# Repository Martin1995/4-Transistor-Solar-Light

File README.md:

# 4-Transistor-Solar-Light
KiCad Repo with Open Hardware Schematics and Board Files for building of small garden solar lights

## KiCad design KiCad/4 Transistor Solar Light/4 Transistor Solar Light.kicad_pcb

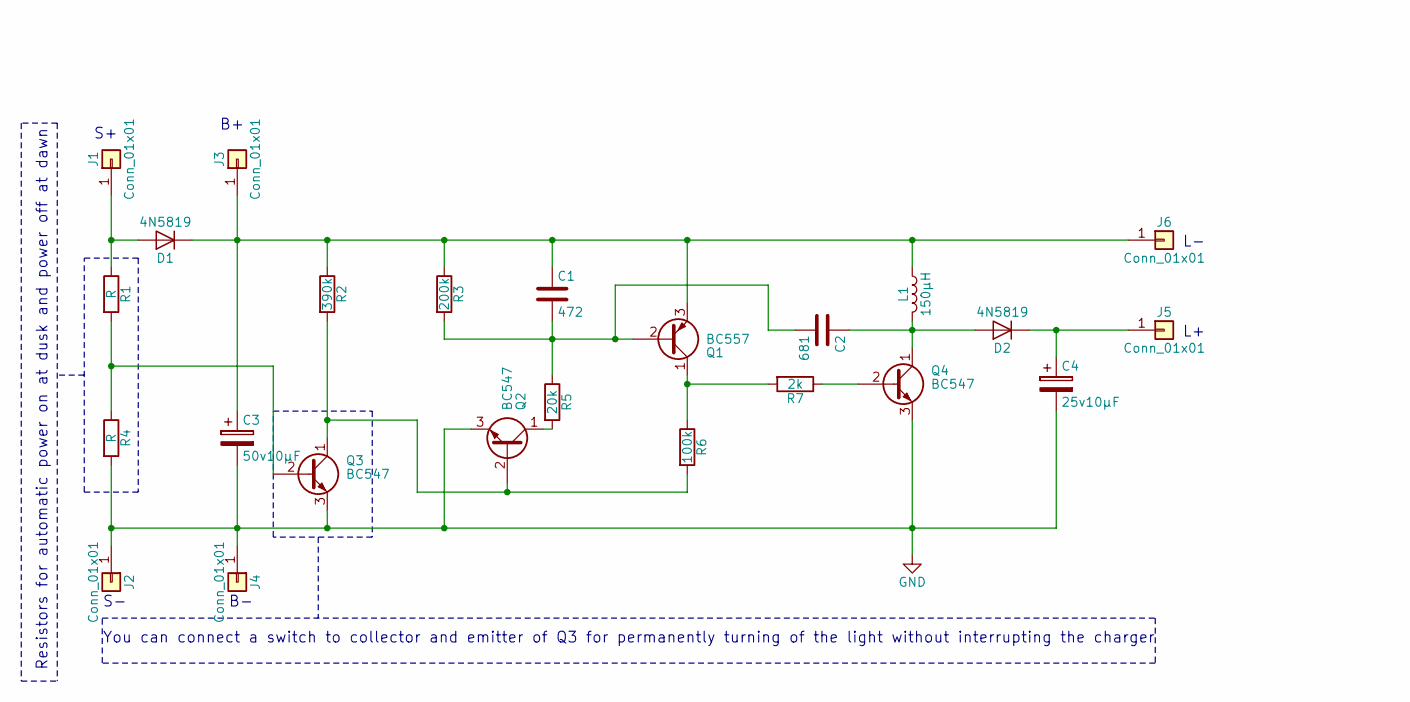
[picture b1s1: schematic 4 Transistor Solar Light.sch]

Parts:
C1: 472; C_Disc_D3.0mm_W1.6mm_P2.50mm
C2: 681; C_Disc_D3.0mm_W1.6mm_P2.50mm
C3: 50v10µF; CP_Radial_D5.0mm_P2.50mm
C4: 25v10µF; CP_Radial_D5.0mm_P2.50mm
D1, D2: 4N5819; D_A-405_P7.62mm_Horizontal
J1, J2, J3, J4, J5, J6: Conn_01x01; Pin_Header_Straight_1x01_Pitch2.00mm
L1: 150µH; L_Axial_L5.3mm_D2.2mm_P7.62mm_Horizontal_Vishay_IM-1
Q1: BC557; TO-92_Molded_Narrow
Q2, Q3, Q4: BC547; TO-92_Molded_Narrow
R1, R4: R; R_Axial_DIN0204_L3.6mm_D1.6mm_P5.08mm_Horizontal
R2: 390k; R_Axial_DIN0204_L3.6mm_D1.6mm_P5.08mm_Horizontal
R3: 200k; R_Axial_DIN0204_L3.6mm_D1.6mm_P5.08mm_Horizontal
R5: 20k; R_Axial_DIN0204_L3.6mm_D1.6mm_P5.08mm_Horizontal
R6: 100k; R_Axial_DIN0204_L3.6mm_D1.6mm_P5.08mm_Horizontal
R7: 2k; R_Axial_DIN0204_L3.6mm_D1.6mm_P5.08mm_Horizontal

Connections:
GND: C3.2, C4.2, J2.1, J4.1, Q2.3 (E), Q3.3 (E), Q4.3 (E), R4.2
unnamed: C1.1, C3.1, D1.1 (K), J3.1, J6.1, L1.1, Q1.3 (E), R2.1, R3.1
unnamed: C1.2, C2.2, Q1.2 (B), R3.2, R5.1
unnamed: C2.1, D2.2 (A), L1.2, Q4.1 (C)
unnamed: C4.1, D2.1 (K), J5.1
unnamed: D1.2 (A), J1.1, R1.1
unnamed: Q1.1 (C), R6.1, R7.2
unnamed: Q2.1 (C), R5.2
unnamed: Q2.2 (B), Q3.1 (C), R2.2, R6.2
unnamed: Q3.2 (B), R1.2, R4.1
unnamed: Q4.2 (B), R7.1

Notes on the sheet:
Resistors for automatic power on at dusk and power off at dawn
You can connect a switch to collector and emitter of Q3 for permanently turning of the light without interrupting the charger

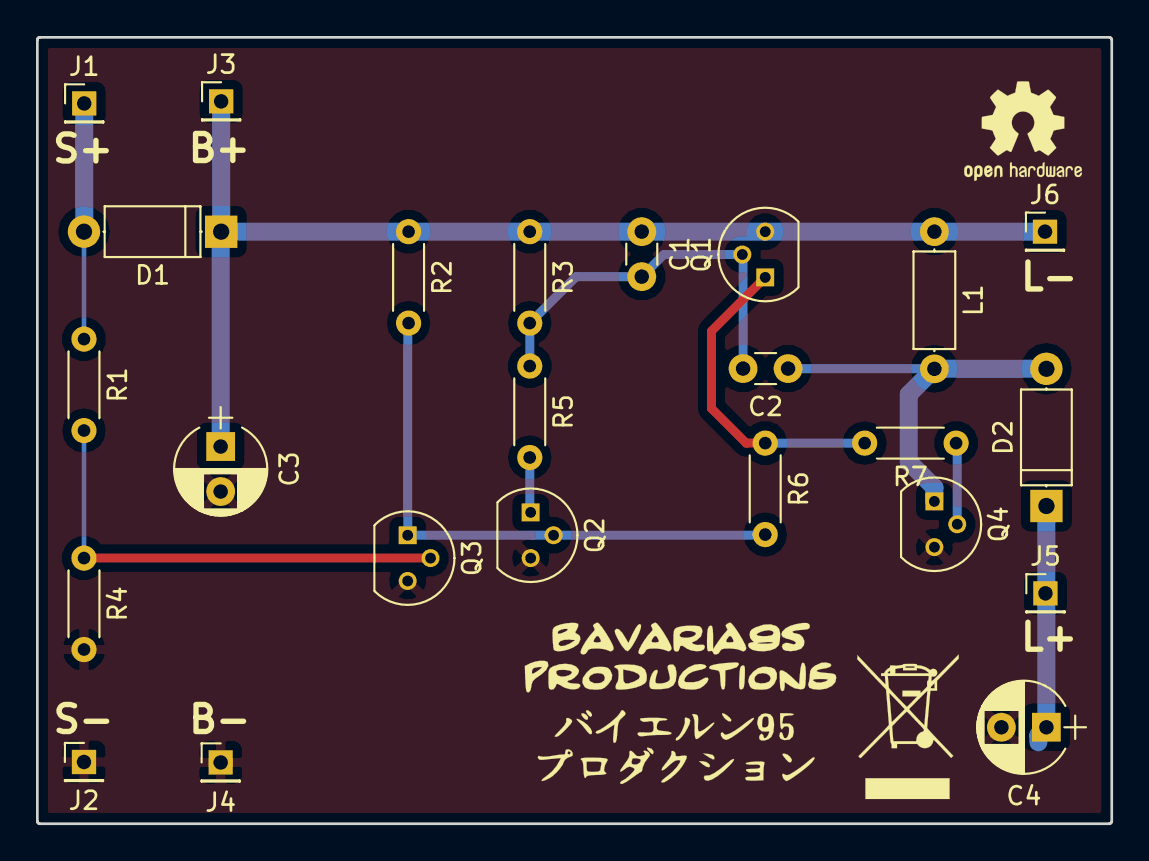
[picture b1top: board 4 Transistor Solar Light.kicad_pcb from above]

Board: 2 copper layers, 59.7 x 43.7 mm, 24 parts (0 on the bottom side), 11 nets.

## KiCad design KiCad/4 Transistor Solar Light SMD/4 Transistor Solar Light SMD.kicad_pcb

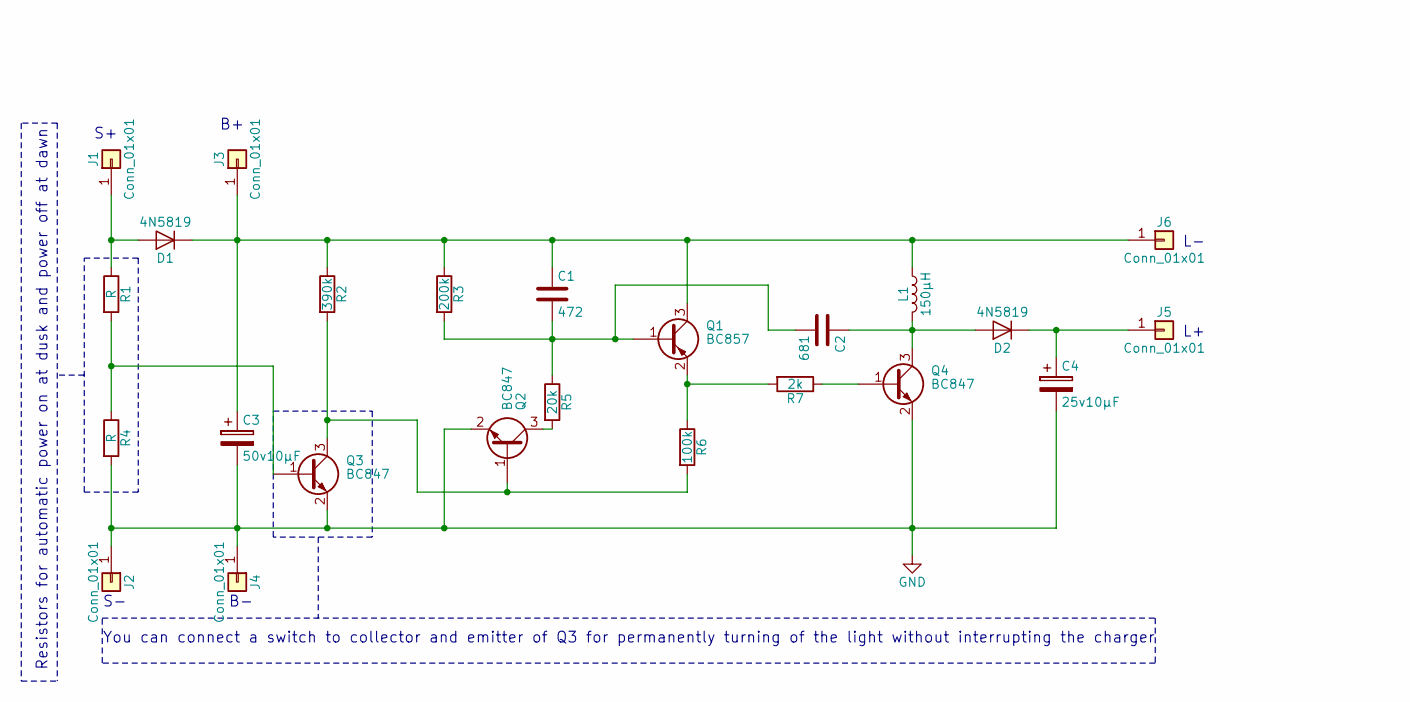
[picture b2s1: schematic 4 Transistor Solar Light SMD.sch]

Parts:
C1: 472; C_0805_HandSoldering
C2: 681; C_0805_HandSoldering
C3: 50v10µF; CP_Elec_4x5.8
C4: 25v10µF; CP_Elec_4x5.8
D1, D2: 4N5819; D_0805
J1, J2, J3, J4, J5, J6: Conn_01x01; Pin_Header_Straight_1x01_Pitch2.00mm
L1: 150µH; L_Axial_L5.3mm_D2.2mm_P7.62mm_Horizontal_Vishay_IM-1
Q1: BC857; SOT-23
Q2, Q3, Q4: BC847; SOT-23
R1, R4: R; R_0805_HandSoldering
R2: 390k; R_0805_HandSoldering
R3: 200k; R_0805_HandSoldering
R5: 20k; R_0805_HandSoldering
R6: 100k; R_0805_HandSoldering
R7: 2k; R_0805_HandSoldering

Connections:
GND: C3.2, C4.2, J2.1, J4.1, Q2.2 (E), Q3.2 (E), Q4.2 (E), R4.2
unnamed: C1.1, C3.1, D1.1 (K), J3.1, J6.1, L1.1, Q1.3 (C), R2.1, R3.1
unnamed: C1.2, C2.2, Q1.1 (B), R3.2, R5.1
unnamed: C2.1, D2.2 (A), L1.2, Q4.3 (C)
unnamed: C4.1, D2.1 (K), J5.1
unnamed: D1.2 (A), J1.1, R1.1
unnamed: Q1.2 (E), R6.1, R7.2
unnamed: Q2.1 (B), Q3.3 (C), R2.2, R6.2
unnamed: Q2.3 (C), R5.2
unnamed: Q3.1 (B), R1.2, R4.1
unnamed: Q4.1 (B), R7.1

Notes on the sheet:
Resistors for automatic power on at dusk and power off at dawn
You can connect a switch to collector and emitter of Q3 for permanently turning of the light without interrupting the charger

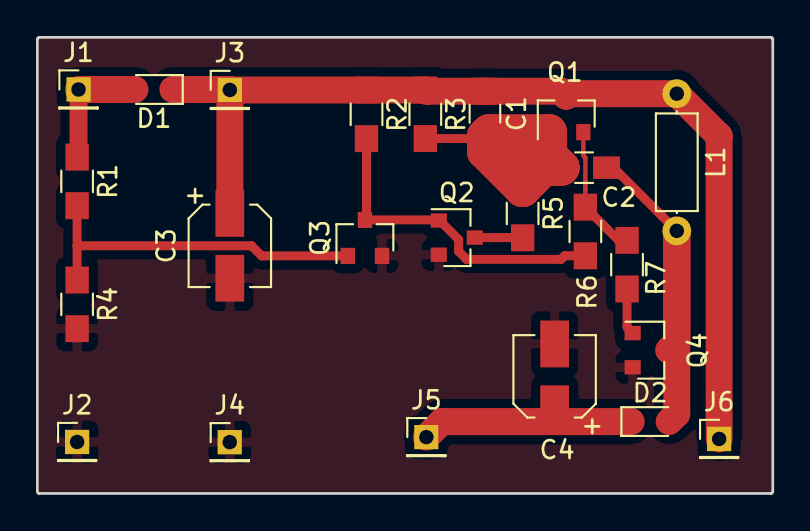
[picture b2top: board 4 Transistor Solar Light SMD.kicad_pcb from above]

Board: 2 copper layers, 40.9 x 25.3 mm, 24 parts (0 on the bottom side), 11 nets.

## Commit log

2018-05-09 Set theme jekyll-theme-cayman
